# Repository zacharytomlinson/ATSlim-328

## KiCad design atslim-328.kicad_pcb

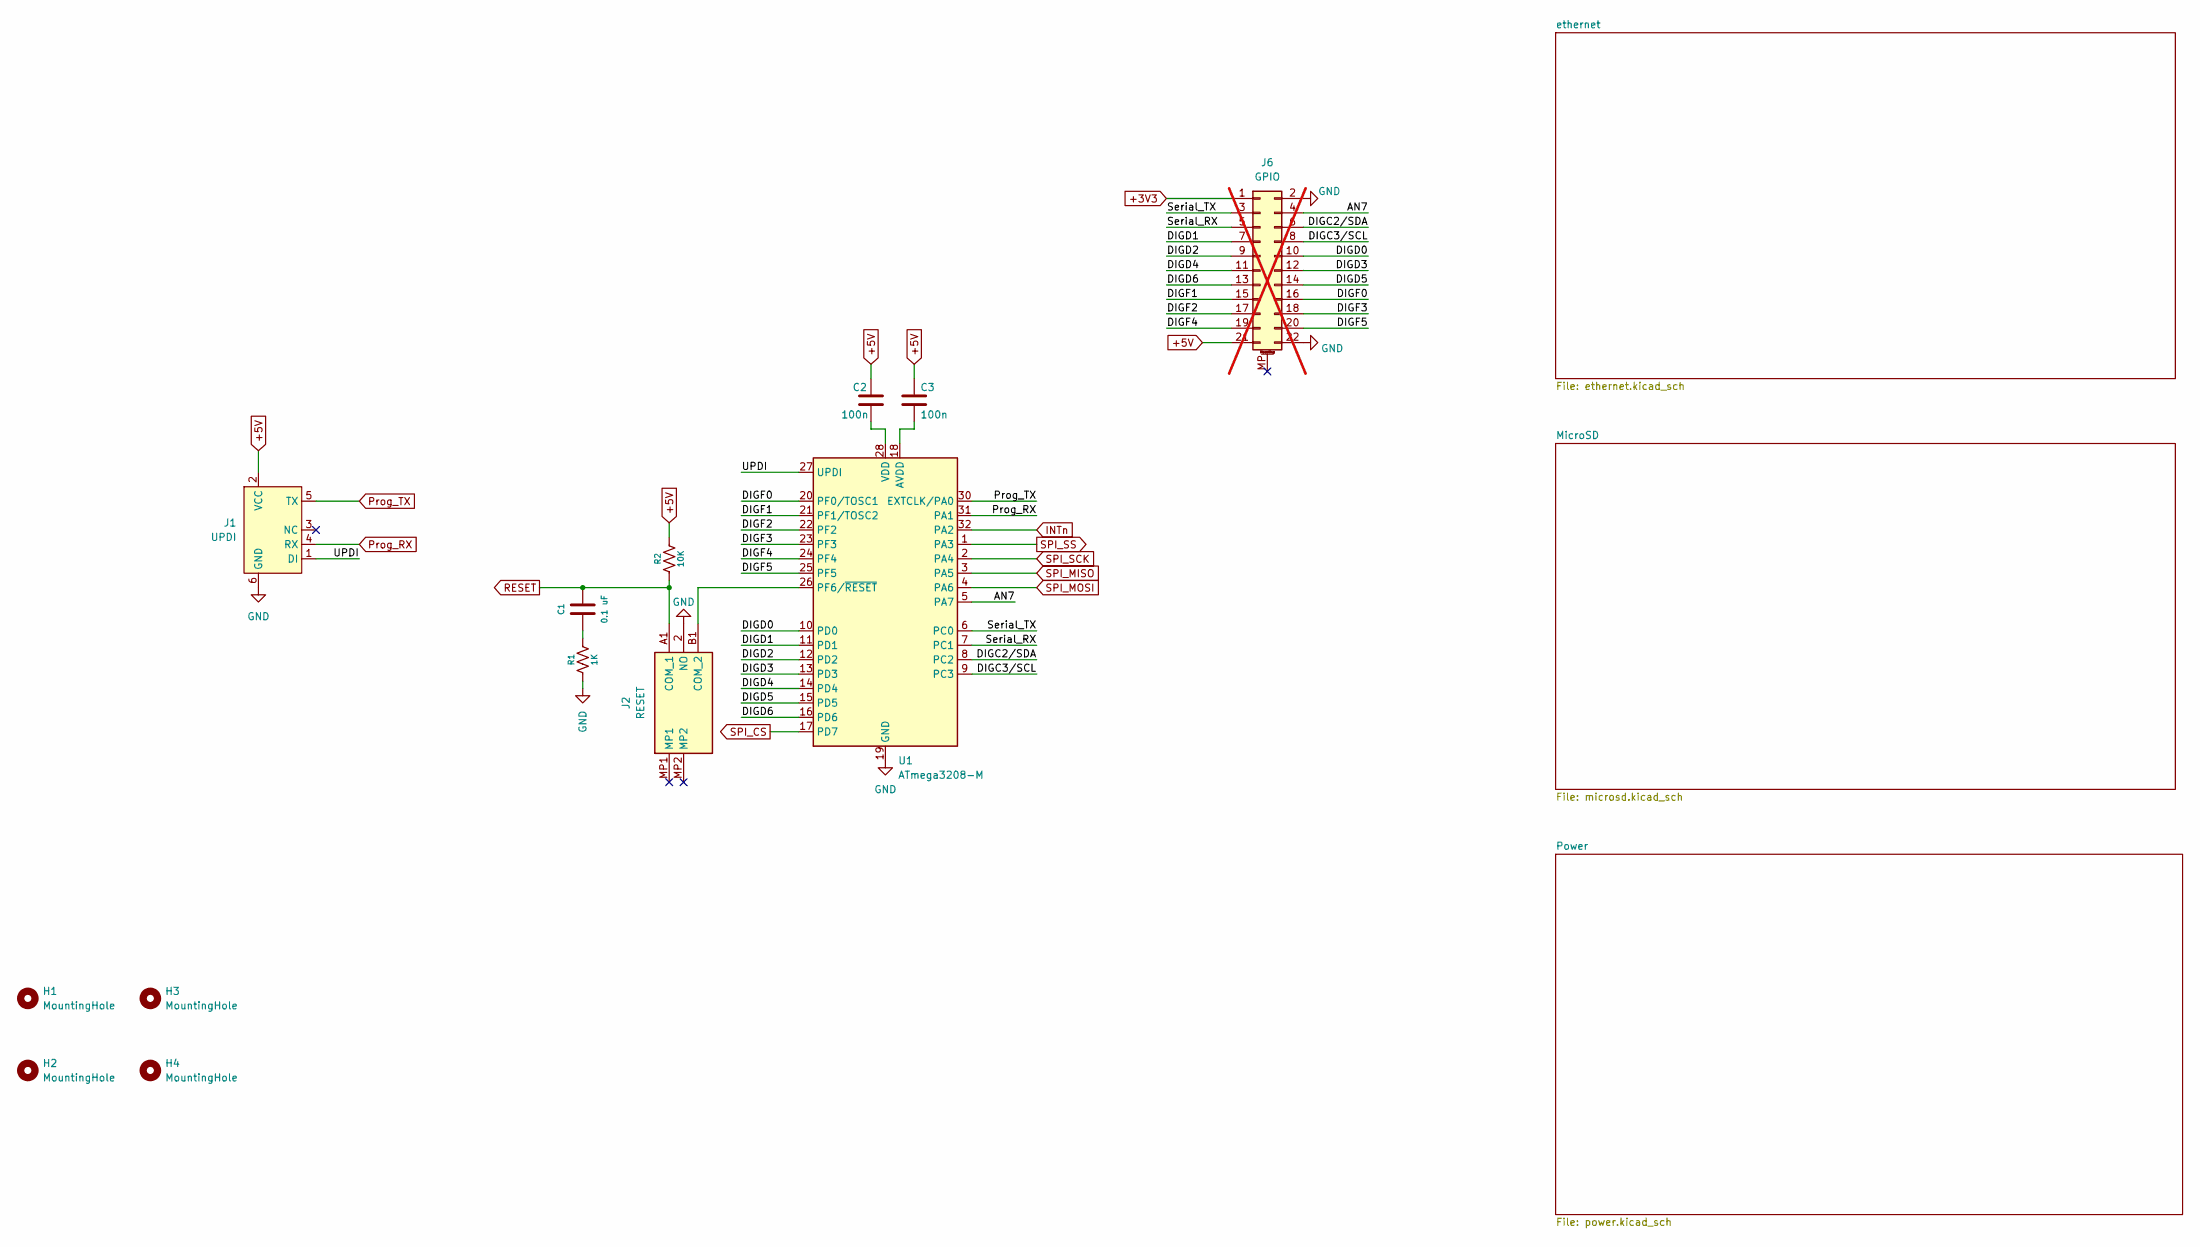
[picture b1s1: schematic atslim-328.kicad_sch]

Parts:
C1: 0.1 uF; C_0402_1005Metric_Pad0.74x0.62mm_HandSolder; MPN C0805C104K1RACAUTO
C2, C3: 100n; C_0402_1005Metric_Pad0.74x0.62mm_HandSolder
H1, H2, H3, H4: MountingHole; RPI_MountingHole
J1: UPDI; Tag-Connect_TC2030-IDC-NL_2x03_P1.27mm_Vertical
J2: RESET; EVPAEDB2A; Mouser Part Number 667-EVP-AEDB2A
J6: GPIO; PinHeader_2x11_P2.54mm_Vertical; not fitted
R1: 1K; R_0402_1005Metric_Pad0.72x0.64mm_HandSolder; MPN CRCW08051K00JNEA
R2: 10K; R_0402_1005Metric_Pad0.72x0.64mm_HandSolder; MPN CRCW080510K0JNEA
U1: ATmega3208-M; QFN-32-1EP_5x5mm_P0.5mm_EP3.1x3.1mm_ThermalVias

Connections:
+3V3: J6.1; also elsewhere on the board
+5V: C2.1, C3.1, J1.2 (VCC), J6.21, R2.2; also elsewhere on the board
/AN7: J6.4, U1.5 (PA7)
/DIGC2/SDA: J6.6, U1.8 (PC2)
/DIGC3/SCL: J6.8, U1.9 (PC3)
/DIGD0: J6.10, U1.10 (PD0)
/DIGD1: J6.7, U1.11 (PD1)
/DIGD2: J6.9, U1.12 (PD2)
/DIGD3: J6.12, U1.13 (PD3)
/DIGD4: J6.11, U1.14 (PD4)
/DIGD5: J6.14, U1.15 (PD5)
/DIGD6: J6.13, U1.16 (PD6)
/DIGF0: J6.16, U1.20 (PF0/TOSC1)
/DIGF1: J6.15, U1.21 (PF1/TOSC2)
/DIGF2: J6.17, U1.22 (PF2)
/DIGF3: J6.18, U1.23 (PF3)
/DIGF4: J6.19, U1.24 (PF4)
/DIGF5: J6.20, U1.25 (PF5)
/Serial_RX: J6.5, U1.7 (PC1)
/Serial_TX: J6.3, U1.6 (PC0)
/UPDI: J1.1 (DI), U1.27 (UPDI)
GND: J1.6 (GND), J2.2 (NO), J6.2, J6.22, R1.1, U1.19 (GND), U1.29 (GND), U1.33 (GND); also elsewhere on the board
INTn: U1.32 (PA2); also elsewhere on the board
unnamed: C1.1, R1.2
unnamed: J2.B1 (COM_2), U1.26 (PF6/~RESET)
unnamed: C3.2, U1.18 (AVDD)
unnamed: C2.2, U1.28 (VDD)
Prog_RX: J1.4 (RX), U1.31 (PA1)
Prog_TX: J1.5 (TX), U1.30 (EXTCLK/PA0)
RESET: C1.2, J2.A1 (COM_1), R2.1; also elsewhere on the board
SPI_CS: U1.17 (PD7); also elsewhere on the board
SPI_MISO: U1.3 (PA5); also elsewhere on the board
SPI_MOSI: U1.4 (PA6); also elsewhere on the board
SPI_SCK: U1.2 (PA4); also elsewhere on the board
SPI_SS: U1.1 (PA3); also elsewhere on the board

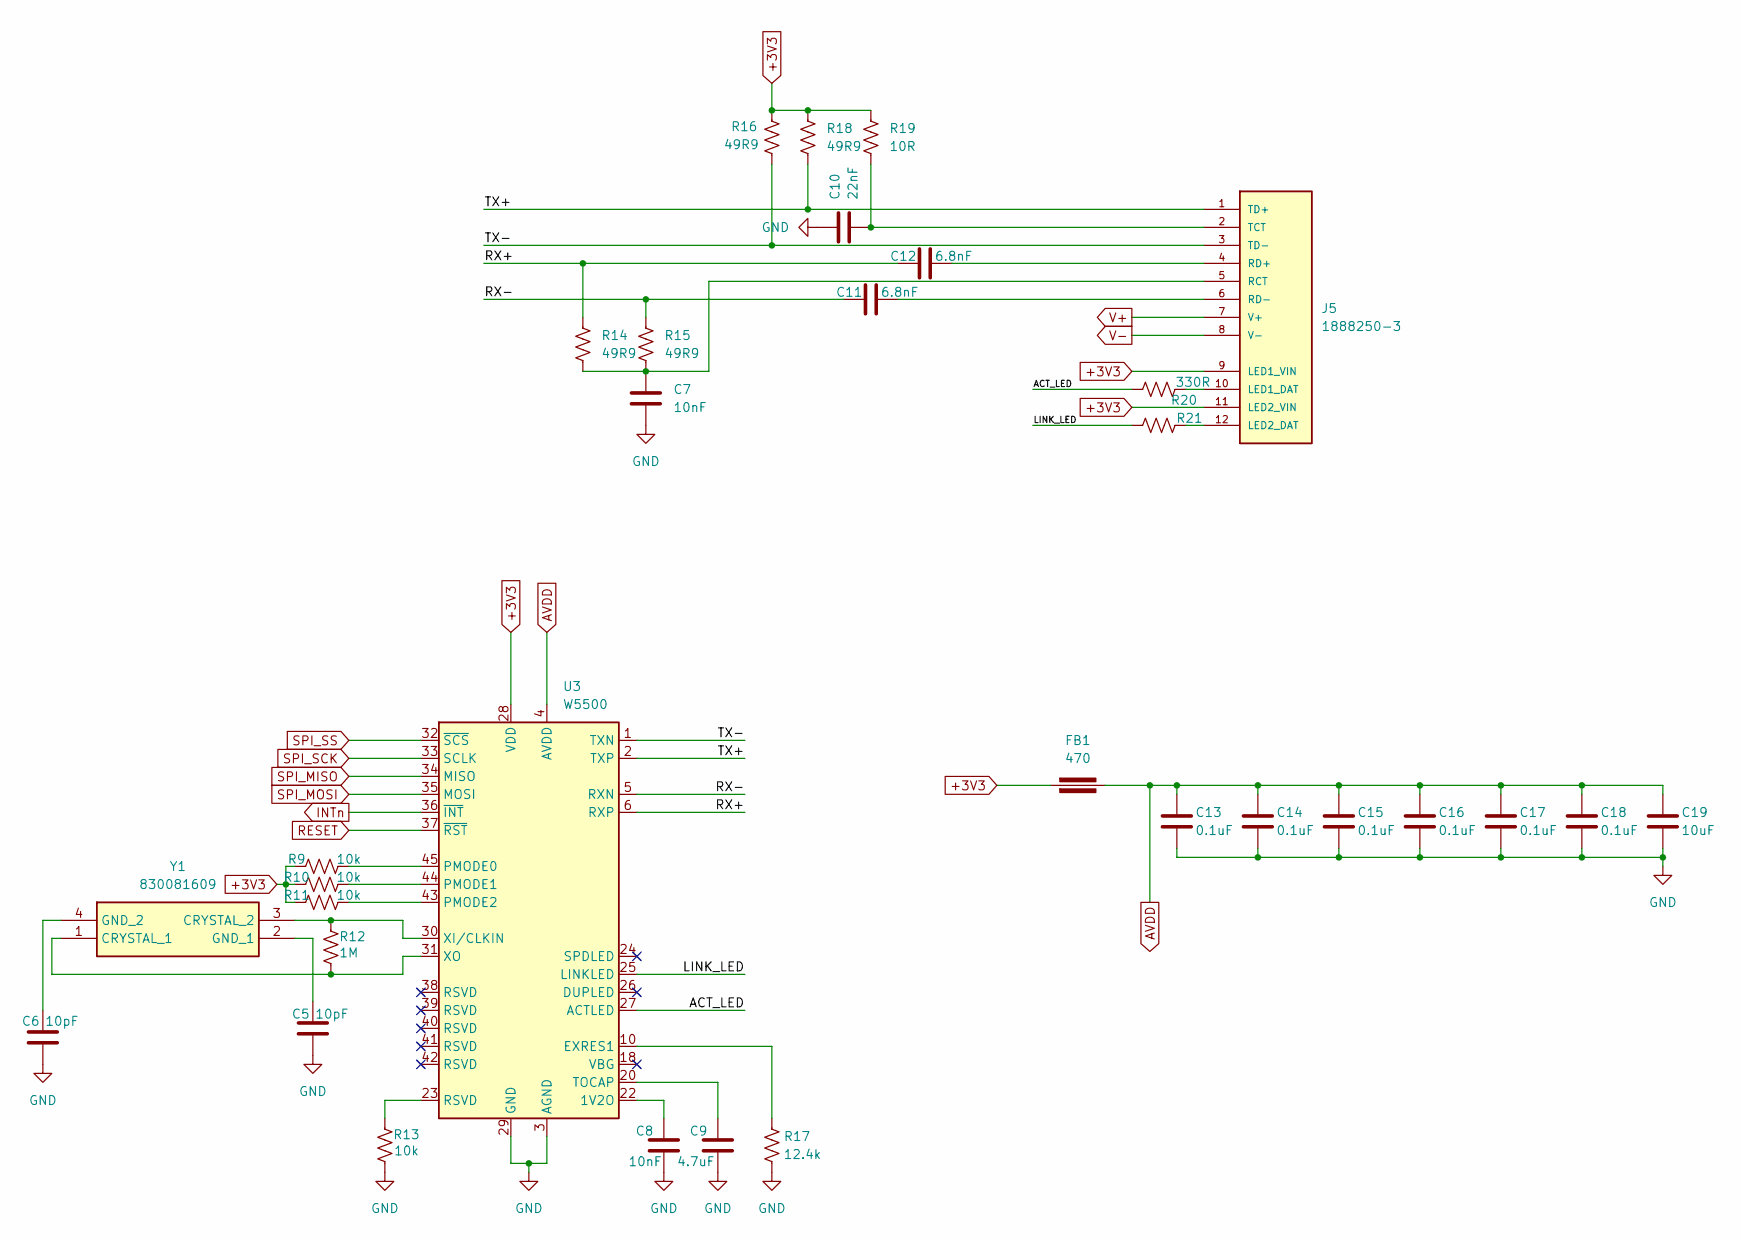
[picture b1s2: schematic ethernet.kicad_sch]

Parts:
C5, C6: 10pF; C_0402_1005Metric_Pad0.74x0.62mm_HandSolder
C7, C8: 10nF; C_0402_1005Metric_Pad0.74x0.62mm_HandSolder
C9: 4.7uF; C_0402_1005Metric_Pad0.74x0.62mm_HandSolder
C10: 22nF; C_0402_1005Metric_Pad0.74x0.62mm_HandSolder
C11, C12: 6.8nF; C_0402_1005Metric_Pad0.74x0.62mm_HandSolder
C13, C14, C15, C16, C17, C18: 0.1uF; C_0402_1005Metric_Pad0.74x0.62mm_HandSolder
C19: 10uF; C_0402_1005Metric_Pad0.74x0.62mm_HandSolder
FB1: 470; Ferrite_1206_3216Metric
J5: 1888250-3; TE_1888250-3; PARTREV D
R9, R10, R11, R13: 10k; R_0402_1005Metric_Pad0.72x0.64mm_HandSolder
R12: 1M; R_0402_1005Metric_Pad0.72x0.64mm_HandSolder
R14, R15, R16, R18: 49R9; R_0402_1005Metric_Pad0.72x0.64mm_HandSolder
R17: 12.4k; R_0402_1005Metric_Pad0.72x0.64mm_HandSolder
R19: 10R; R_0402_1005Metric_Pad0.72x0.64mm_HandSolder
R20, R21: 330R; R_0402_1005Metric_Pad0.72x0.64mm_HandSolder
U3: W5500; LQFP-48_7x7mm_P0.5mm
Y1: 830081609; Manufacturer_Part_Number 830081609

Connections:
+3V3: FB1.1, J5.9 (LED1_VIN), J5.11 (LED2_VIN), R9.2, R10.2, R11.2, R16.1, R18.1, R19.1, U3.28 (VDD); also elsewhere on the board
/ethernet/ACT_LED: R20.2, U3.27 (ACTLED)
/ethernet/LINK_LED: R21.2, U3.25 (LINKLED)
/ethernet/RX+: C12.2, R14.1, U3.6 (RXP)
/ethernet/RX-: C11.2, R15.1, U3.5 (RXN)
/ethernet/TX+: J5.1 (TD+), R18.2, U3.2 (TXP)
/ethernet/TX-: J5.3 (TD-), R16.2, U3.1 (TXN)
AVDD: C13.1, C14.1, C15.1, C16.1, C17.1, C18.1, C19.1, FB1.2, U3.4 (AVDD), U3.8 (AVDD), U3.11 (AVDD), U3.15 (AVDD), U3.17 (AVDD), U3.21 (AVDD)
GND: C5.2, C6.2, C7.2, C8.2, C9.2, C10.1, C13.2, C14.2, C15.2, C16.2, C17.2, C18.2, C19.2, R13.1, R17.1, U3.3 (AGND), U3.9 (AGND), U3.14 (AGND), U3.16 (AGND), U3.19 (AGND), U3.29 (GND), U3.48 (AGND); also elsewhere on the board
INTn: U3.36 (~INT); also elsewhere on the board
unnamed: J5.10 (LED1_DAT), R20.1
unnamed: J5.12 (LED2_DAT), R21.1
unnamed: C7.1, J5.5 (RCT), R14.2, R15.2
unnamed: C12.1, J5.4 (RD+)
unnamed: C11.1, J5.6 (RD-)
unnamed: C10.2, J5.2 (TCT), R19.2
unnamed: R13.2, U3.23 (RSVD)
unnamed: C8.1, U3.22 (1V2O)
unnamed: R17.2, U3.10 (EXRES1)
unnamed: R9.1, U3.45 (PMODE0)
unnamed: R10.1, U3.44 (PMODE1)
unnamed: R11.1, U3.43 (PMODE2)
unnamed: C9.1, U3.20 (TOCAP)
unnamed: R12.2, U3.30 (XI/CLKIN), Y1.3 (CRYSTAL_2)
unnamed: R12.1, U3.31 (XO), Y1.1 (CRYSTAL_1)
unnamed: C5.1, Y1.2 (GND_1)
unnamed: C6.1, Y1.4 (GND_2)
RESET: U3.37 (~RST); also elsewhere on the board
SPI_MISO: U3.34 (MISO); also elsewhere on the board
SPI_MOSI: U3.35 (MOSI); also elsewhere on the board
SPI_SCK: U3.33 (SCLK); also elsewhere on the board
SPI_SS: U3.32 (~SCS); also elsewhere on the board
V+: J5.7 (V+); also elsewhere on the board
V-: J5.8 (V-); also elsewhere on the board

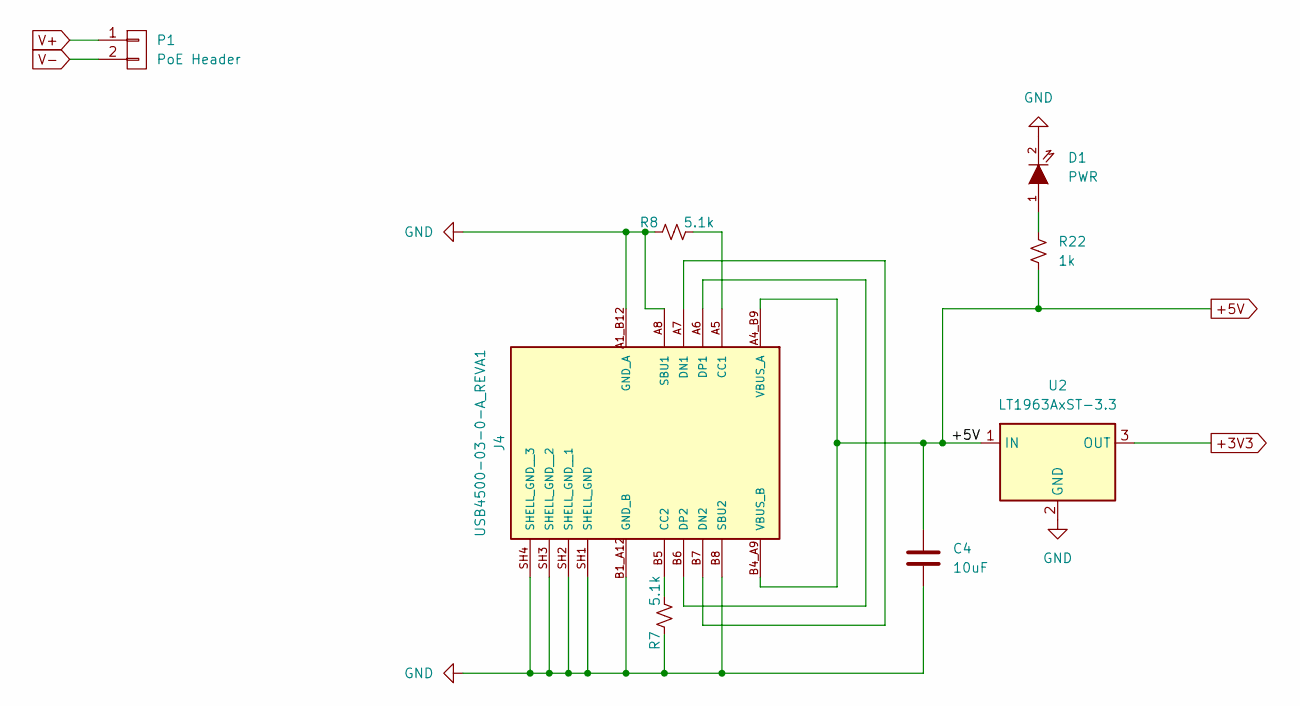
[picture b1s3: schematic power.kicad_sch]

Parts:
C4: 10uF; C_0402_1005Metric_Pad0.74x0.62mm_HandSolder
D1: PWR; LED_1206_3216Metric_Pad1.42x1.75mm_HandSolder
J4: USB4500-03-0-A_REVA1; GCT_USB4500-03-0-A_REVA1; PARTREV A1
P1: PoE Header; PinHeader_1x02_P2.54mm_Vertical
R7, R8: 5.1k; R_0402_1005Metric_Pad0.72x0.64mm_HandSolder
R22: 1k; R_0402_1005Metric_Pad0.72x0.64mm_HandSolder
U2: LT1963AxST-3.3; SOT-223-3_TabPin2

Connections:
+3V3: U2.3 (OUT); also elsewhere on the board
+5V: C4.1, J4.A4_B9 (VBUS_A), J4.B4_A9 (VBUS_B), R22.2, U2.1 (IN); also elsewhere on the board
GND: C4.2, D1.2 (K), J4.A1_B12 (GND_A), J4.A8 (SBU1), J4.B1_A12 (GND_B), J4.B8 (SBU2), J4.SH1 (SHELL_GND), J4.SH2 (SHELL_GND__1), J4.SH3 (SHELL_GND__2), J4.SH4 (SHELL_GND__3), R7.1, R8.1, U2.2 (GND); also elsewhere on the board
unnamed: D1.1 (A), R22.1
unnamed: J4.A5 (CC1), R8.2
unnamed: J4.B5 (CC2), R7.2
unnamed: J4.A7 (DN1), J4.B7 (DN2)
unnamed: J4.A6 (DP1), J4.B6 (DP2)
V+: P1.1; also elsewhere on the board
V-: P1.2; also elsewhere on the board

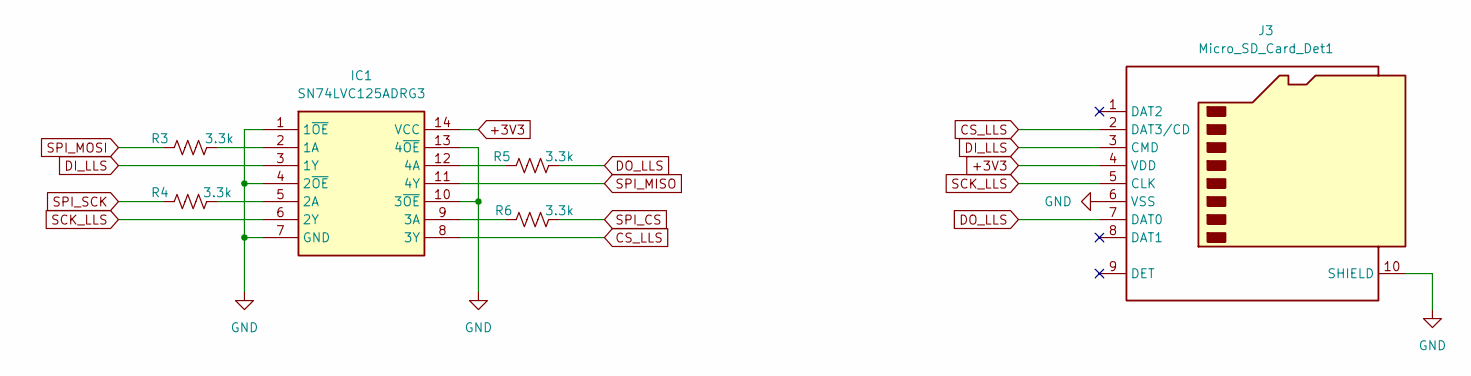
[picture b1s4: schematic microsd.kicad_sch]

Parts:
IC1: SN74LVC125ADRG3; SOIC127P600X175-14N; Mouser Part Number 595-SN74LVC125ADRG3
J3: Micro_SD_Card_Det1; microSD_HC_Wuerth_693072010801
R3, R4, R5, R6: 3.3k; R_0402_1005Metric_Pad0.72x0.64mm_HandSolder

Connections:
+3V3: IC1.14 (VCC), J3.4 (VDD); also elsewhere on the board
CS_LLS: IC1.8 (3Y), J3.2 (DAT3/CD)
DI_LLS: IC1.3 (1Y), J3.3 (CMD)
DO_LLS: J3.7 (DAT0), R5.2
GND: IC1.1 (1~OE), IC1.4 (2~OE), IC1.7 (GND), IC1.10 (3~OE), IC1.13 (4~OE), J3.6 (VSS), J3.10 (SHIELD); also elsewhere on the board
unnamed: IC1.2 (1A), R3.2
unnamed: IC1.5 (2A), R4.2
unnamed: IC1.9 (3A), R6.1
unnamed: IC1.12 (4A), R5.1
SCK_LLS: IC1.6 (2Y), J3.5 (CLK)
SPI_CS: R6.2; also elsewhere on the board
SPI_MISO: IC1.11 (4Y); also elsewhere on the board
SPI_MOSI: R3.1; also elsewhere on the board
SPI_SCK: R4.1; also elsewhere on the board

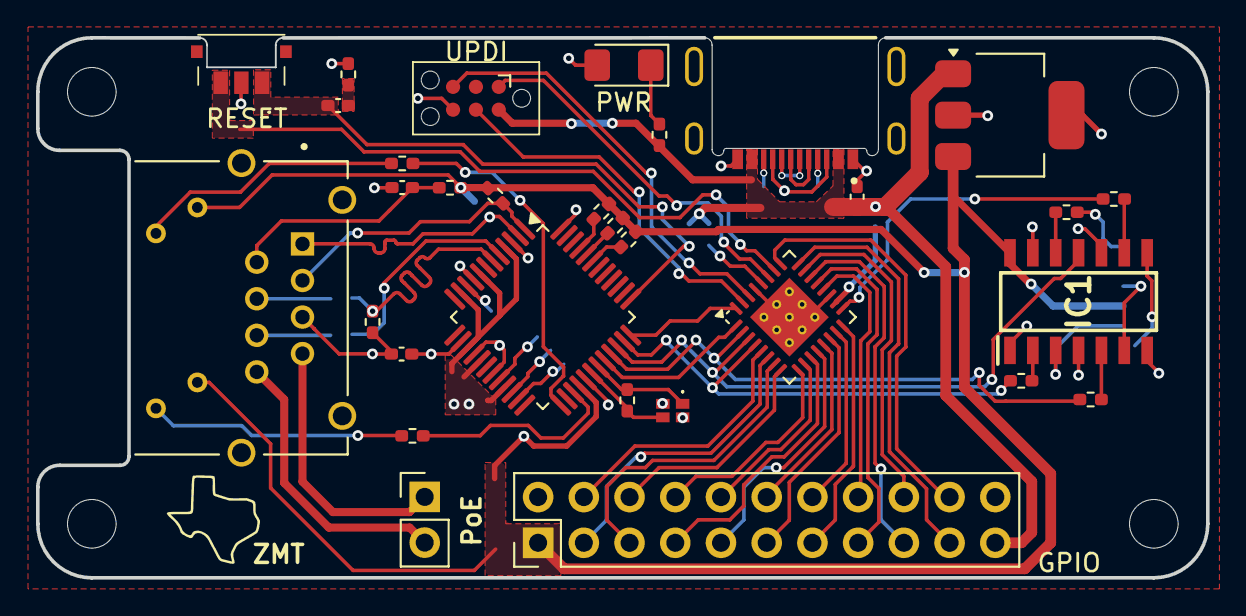
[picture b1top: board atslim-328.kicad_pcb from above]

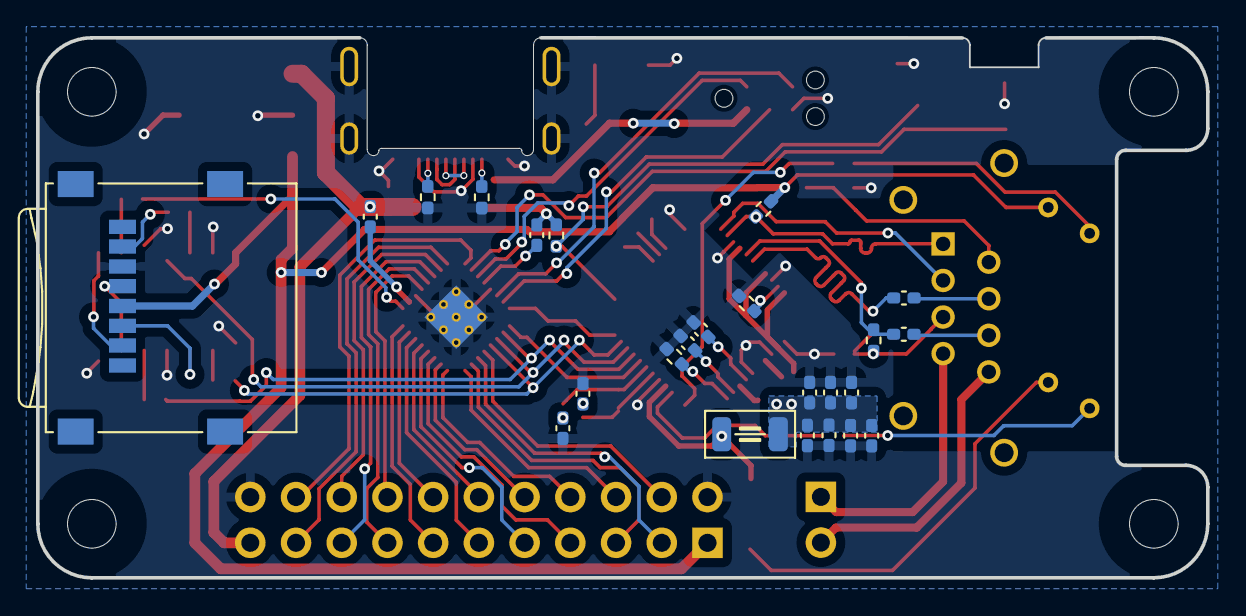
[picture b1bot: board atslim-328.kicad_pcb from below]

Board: 2 copper layers, 65.0 x 30.0 mm, 59 parts (24 on the bottom side), 74 nets.

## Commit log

2024-07-23 Reinit without temp files
2024-07-23 Added imgs of 3D view
2024-07-23 Create README.md
    Added readme to display 3D images
2024-07-23 Cleanup and added PoE header
2024-07-23 Sent off to manufacturer for test articles
2024-07-23 update gitignore for a couple of manufacturing artifacts
2024-07-23 updated 3D images
2024-08-16 Recent updates
2024-08-20 Fucked up UPDI... of course
